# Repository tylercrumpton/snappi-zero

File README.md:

# SNAPpi Zero
Raspberry Pi Zero HAT with a Synapse SNAP module.

![pcb-top] ![pcb-bottom]

## Overview
The **SNAPpi Zero** is a HAT ("Hardware Attached on Top") for the Raspberry Pi Zero board.
It adds a Synapse RF- or SM-series 802.15.4 wireless module that can be programmed using the
SNAPpy language, based on Python.

## Operation
The **SNAPpi Zero**'s SNAP module is connected via UART1 to the Raspberry Pi's UART GPIO pins.
Additionally, the SNAP module's reset pin is connected to a Raspberry Pi, and three SNAP GPIO
are hooked up to LEDs on the **SNAPpi Zero** board. The pin mappings are as follows:

| Description | RF Module Pin | SM Module Pin | Raspberry Pi GPIO |
|-------------|---------------|---------------|-------------------|
| SNAP RX1    | 9             | G4            | BCM 14            |
| SNAP TX1    | 10            | H4            | BCM 15            |
| SNAP Reset  | 23            | H5            | BCM 17            |
| LED A       | 4             | D1            | N/A               |
| LED B       | 3             | D2            | N/A               |
| LED C       | 2             | D3            | N/A               |

[pcb-top]: https://cloud.githubusercontent.com/assets/1317406/22275825/f1805148-e274-11e6-8883-3e8dbbb4946e.png
[pcb-bottom]: https://cloud.githubusercontent.com/assets/1317406/22275830/f65ffa56-e274-11e6-8890-72a585ec53ba.png

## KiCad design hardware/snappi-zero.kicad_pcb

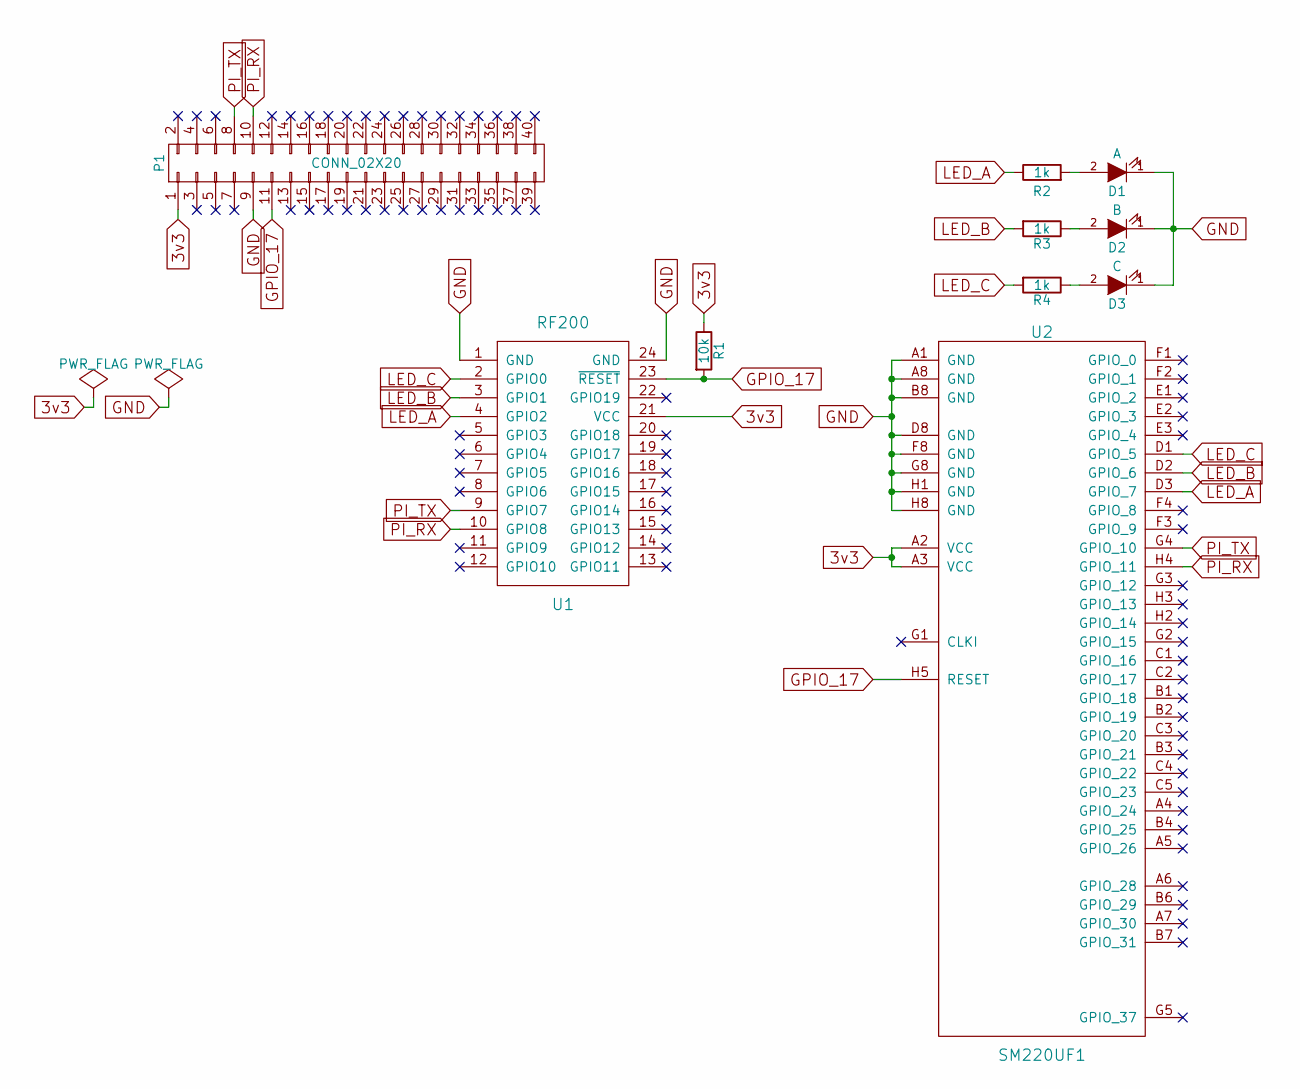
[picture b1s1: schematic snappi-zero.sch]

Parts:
D1: A; LED_1206
D2: B; LED_1206
D3: C; LED_1206
P1: CONN_02X20; Raspberry_Pi_Zero
R1: 10k; R_0805_HandSoldering
R2, R3, R4: 1k; R_0805_HandSoldering
U1: RF200; RF200_nosilk
U2: SM220UF1; SM200_nosilk

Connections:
3v3: P1.1, R1.1, U1.21 (VCC), U2.A2 (VCC), U2.A3 (VCC)
GND: D1.1 (K), D2.1 (K), D3.1 (K), P1.9, U1.1 (GND), U1.24 (GND), U2.A1 (GND), U2.A8 (GND), U2.B8 (GND), U2.D8 (GND), U2.F8 (GND), U2.G8 (GND), U2.H1 (GND), U2.H8 (GND)
GPIO_17: P1.11, R1.2, U1.23 (~RESET), U2.H5 (RESET)
LED_A: R2.1, U1.4 (GPIO2), U2.D3 (GPIO_7)
LED_B: R3.2, U1.3 (GPIO1), U2.D2 (GPIO_6)
LED_C: R4.2, U1.2 (GPIO0), U2.D1 (GPIO_5)
unnamed: D1.2 (A), R2.2
unnamed: D2.2 (A), R3.1
unnamed: D3.2 (A), R4.1
PI_RX: P1.10, U1.10 (GPIO8), U2.H4 (GPIO_11)
PI_TX: P1.8, U1.9 (GPIO7), U2.G4 (GPIO_10)

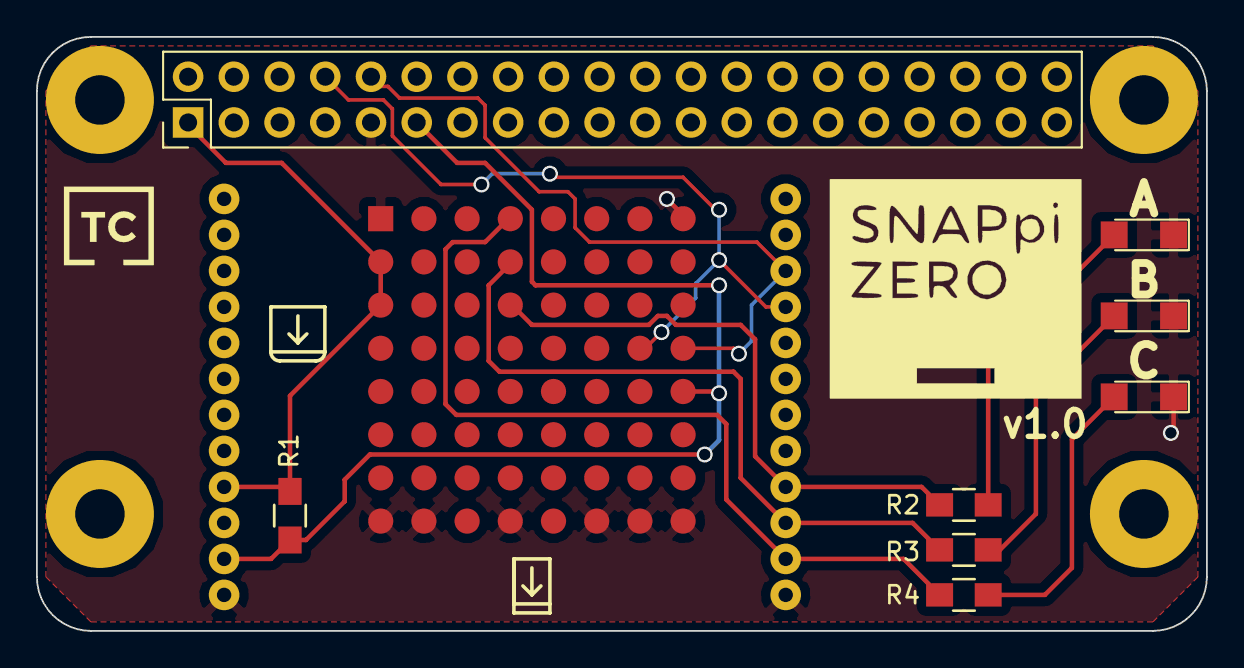
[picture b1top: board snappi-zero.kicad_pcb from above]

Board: 2 copper layers, 65.0 x 33.0 mm, 11 parts (0 on the bottom side), 11 nets.

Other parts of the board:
svg2mod: G***; tc_30mm

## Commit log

2017-01-20 Create initial project setup.
2017-01-20 Update to latest CrumpPrints to get RPi Zero.
2017-01-21 Design schematic.
2017-01-22 Add LEDs and footprint assignment.
2017-01-22 Fix Pi Zero connector pin count.
2017-01-22 Update CrumpPrints to get new nosilk modules.
2017-01-23 Place and route initial board.
2017-01-23 Add TC logo and finalize PCB.
2017-01-29 Fix missing TX/RX pins on SM modules.
2017-01-29 Removed 'special' from libraries.
2017-01-29 Fix Pi RX/TX pins.
2017-01-29 Add pin information to README.
2017-01-29 Add board images to README.
2017-02-03 Improve PCB copper pour shape.

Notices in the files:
hardware/snappi-zero.kicad_pcb:
CC-BY-SA 4.0
